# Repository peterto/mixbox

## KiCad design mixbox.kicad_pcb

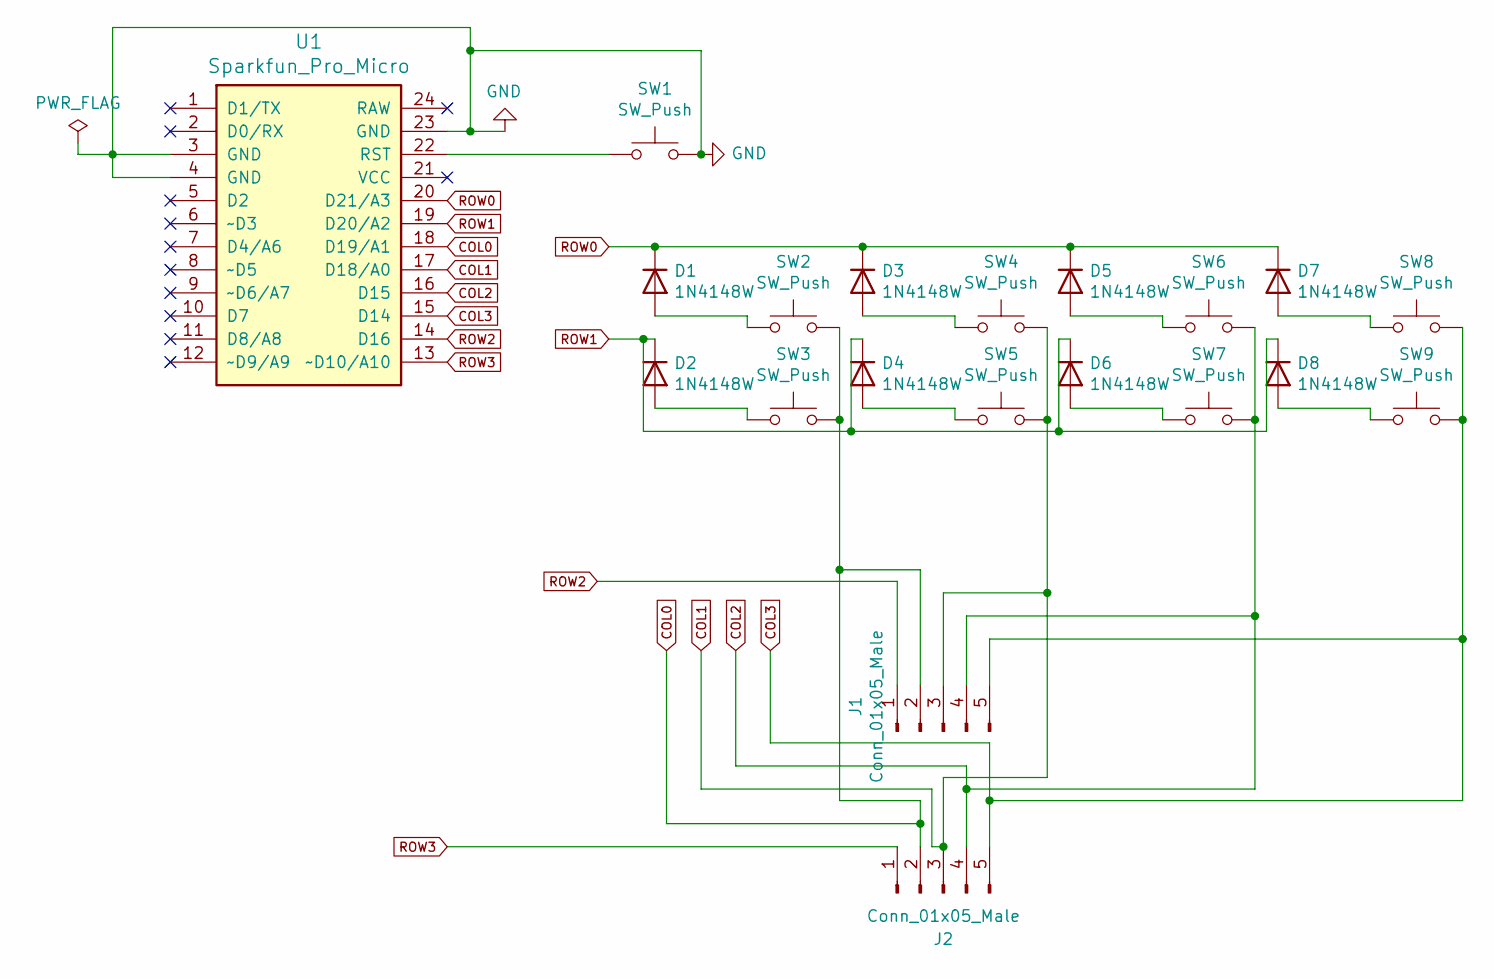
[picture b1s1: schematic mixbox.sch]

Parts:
D1, D2, D3, D4, D5, D6, D7, D8: 1N4148W; D_SOD-123
J1, J2: Conn_01x05_Male; JST_PH_S5B-PH-K_1x05_P2.00mm_Horizontal
SW1: SW_Push; SW_PUSH_6mm
SW2, SW3, SW4, SW5, SW6, SW7, SW8, SW9: SW_Push; Kailh_socket_MX_optional
U1: Sparkfun_Pro_Micro

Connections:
COL0: J1.2, J2.2, SW2.2, SW3.2, U1.18 (D19/A1)
COL1: J1.3, J2.3, SW4.2, SW5.2, U1.17 (D18/A0)
COL2: J1.4, J2.4, SW6.2, SW7.2, U1.16 (D15)
COL3: J1.5, J2.5, SW8.2, SW9.2, U1.15 (D14)
GND: SW1.2, U1.3 (GND), U1.4 (GND), U1.23 (GND)
unnamed: D1.2 (A), SW2.1
unnamed: D2.2 (A), SW3.1
unnamed: D3.2 (A), SW4.1
unnamed: D4.2 (A), SW5.1
unnamed: D5.2 (A), SW6.1
unnamed: D6.2 (A), SW7.1
unnamed: D7.2 (A), SW8.1
unnamed: D8.2 (A), SW9.1
unnamed: SW1.1, U1.22 (RST)
ROW0: D1.1 (K), D3.1 (K), D5.1 (K), D7.1 (K), U1.20 (D21/A3)
ROW1: D2.1 (K), D4.1 (K), D6.1 (K), D8.1 (K), U1.19 (D20/A2)
ROW2: J1.1, U1.14 (D16)
ROW3: J2.1, U1.13 (~~D10/A10)

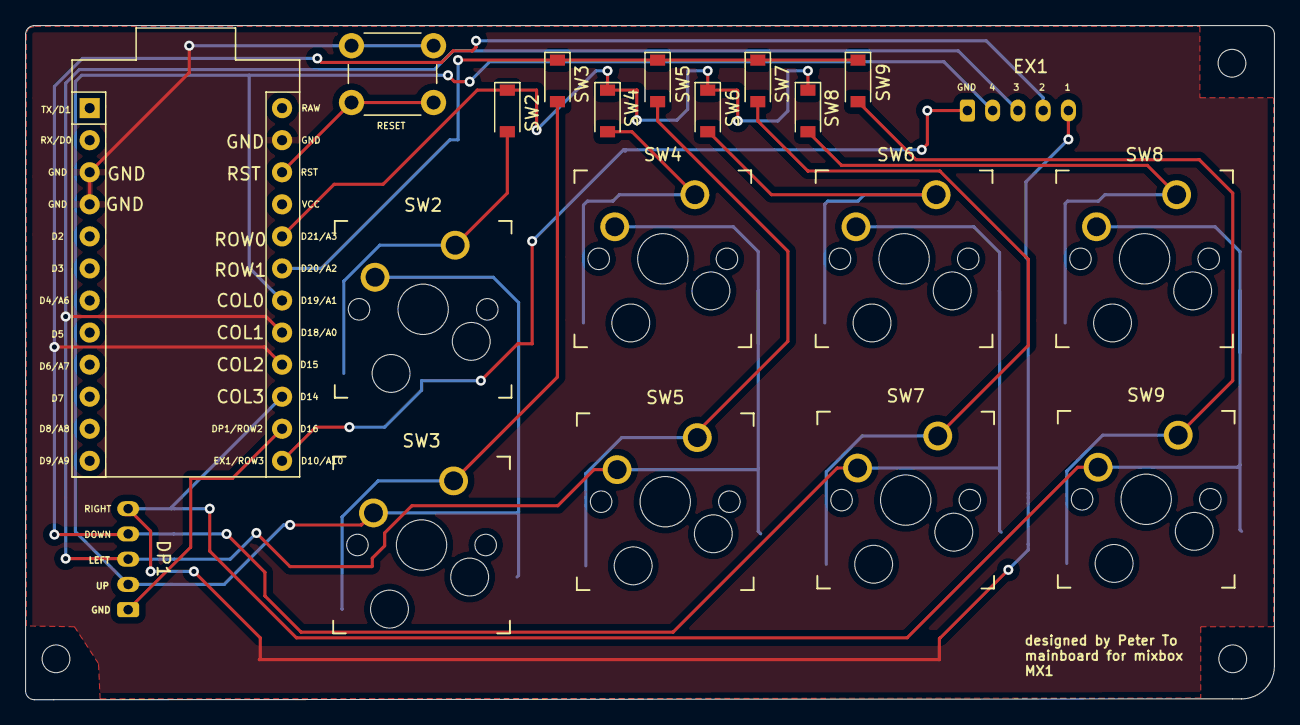
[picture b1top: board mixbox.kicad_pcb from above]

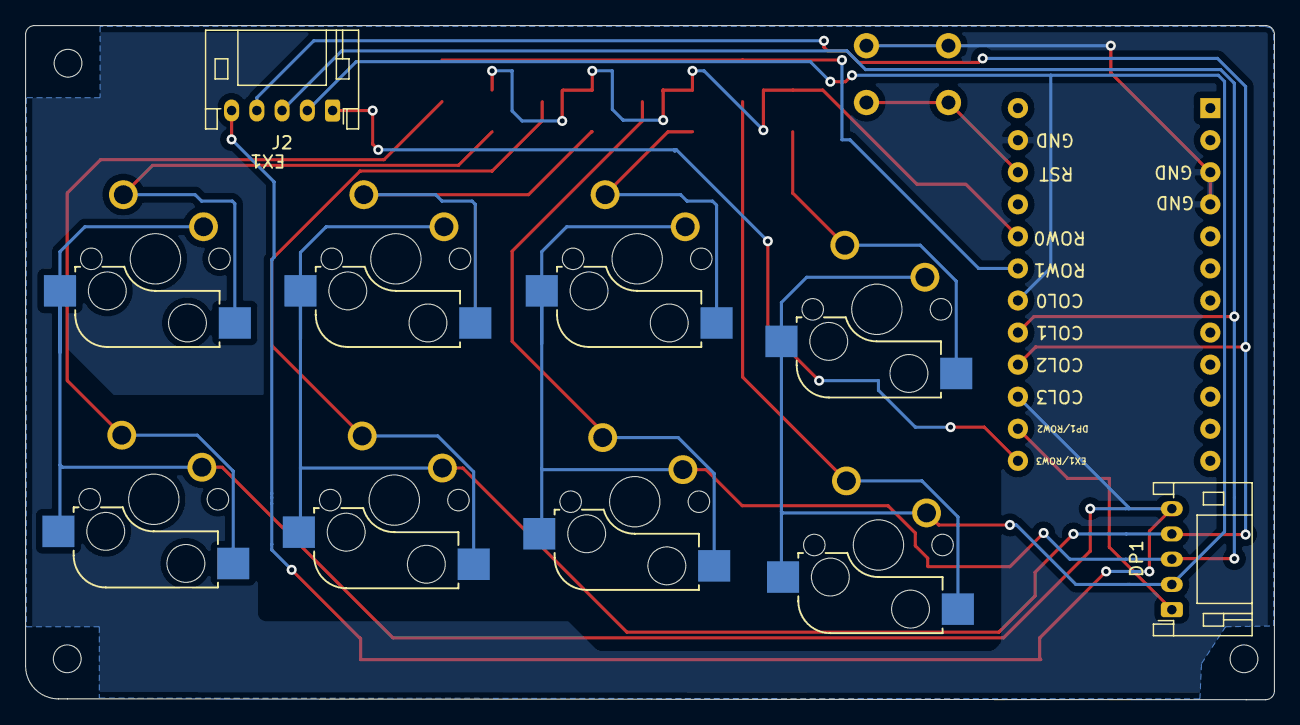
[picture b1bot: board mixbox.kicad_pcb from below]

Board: 2 copper layers, 98.9 x 53.4 mm, 20 parts (2 on the bottom side), 18 nets.

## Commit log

2022-01-02 Updates schematic for 2 extra rows and columns from direct pin from the J1 and J2 connectors
2022-01-02 Updates rows and columns in pcbnew and updates J2 from 1x06 to 1x05 connector
2022-01-02 Adds pwr_flag to schematic gnd
2022-01-02 Updates columns to terminate at the J2 end instead of the first row of the face buttons
